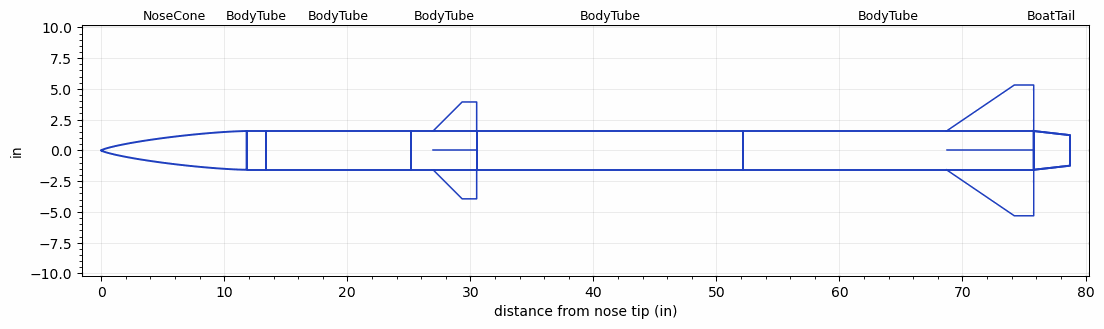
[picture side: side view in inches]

<RASAeroDocument>
 <FileVersion>2</FileVersion>
 <RocketDesign>
  <NoseCone>
   <Length>11.811</Length>
   <Diameter>3.1496</Diameter>
   <Shape>Von Karman Ogive</Shape>
   <Location>0</Location>
  </NoseCone>
  <BodyTube>
   <Length>1.5748</Length>
   <Diameter>3.1496</Diameter>
   <Location>11.811</Location>
  </BodyTube>
  <BodyTube>
   <Length>11.811</Length>
   <Diameter>3.1496</Diameter>
   <Location>13.3858</Location>
  </BodyTube>
  <BodyTube>
   <Length>5.3149</Length>
   <Diameter>3.1496</Diameter>
   <Location>25.1968</Location>
   <Fin>
    <Count>4</Count>
    <Chord>3.5433</Chord>
    <Span>2.3622</Span>
    <SweepDistance>2.3622</SweepDistance>
    <TipChord>1.1811</TipChord>
    <Thickness>0.1181</Thickness>
    <Location>3.5433</Location>
    <AirfoilSection>Subsonic NACA</AirfoilSection>
   </Fin>
  </BodyTube>
  <BodyTube>
   <Length>21.6535</Length>
   <Diameter>3.1496</Diameter>
   <Location>30.5117</Location>
  </BodyTube>
  <BodyTube>
   <Length>23.622</Length>
   <Diameter>3.1496</Diameter>
   <Location>52.1652</Location>
   <BoattailLength>2.9528</BoattailLength>
   <BoattailRearDiameter>2.4803</BoattailRearDiameter>
   <Fin>
    <Count>4</Count>
    <Chord>7.0866</Chord>
    <Span>3.7402</Span>
    <SweepDistance>5.5118</SweepDistance>
    <TipChord>1.5748</TipChord>
    <Thickness>0.1181</Thickness>
    <Location>7.0866</Location>
    <AirfoilSection>Rounded</AirfoilSection>
   </Fin>
  </BodyTube>
  <BoatTail>
   <Length>2.9528</Length>
   <Diameter>3.1496</Diameter>
   <RearDiameter>2.4803</RearDiameter>
   <Location>75.7872</Location>
  </BoatTail>
  <Surface>Rough Camouflage Paint</Surface>
  <ModifiedBarrowman>False</ModifiedBarrowman>
  <Turbulence>False</Turbulence>
  <UseBooster1>False</UseBooster1>
  <UseBooster2>False</UseBooster2>
  <Comments>Ready for PDR!</Comments>
 </RocketDesign>
 <LaunchSite>
  <Altitude>0</Altitude>
  <Pressure>29.9214</Pressure>
  <RodAngle>0</RodAngle>
  <RodLength>157.48</RodLength>
  <Temperature>59</Temperature>
  <WindSpeed>4.4739</WindSpeed>
 </LaunchSite>
 <Recovery>
  <Altitude1>984.252</Altitude1>
  <Altitude2>656.168</Altitude2>
  <DeviceType1>Parachute</DeviceType1>
  <DeviceType2>Parachute</DeviceType2>
  <Event1>True</Event1>
  <Event2>True</Event2>
  <Size1>25.9999</Size1>
  <Size2>15</Size2>
  <EventType1>Altitude</EventType1>
  <EventType2>Apogee</EventType2>
  <CD1>0.75</CD1>
  <CD2>0</CD2>
 </Recovery>
 <SimulationList>
  <Simulation>
   <SustainerLaunchWt>15.1929</SustainerLaunchWt>
   <SustainerCG>47.4662</SustainerCG>
   <SustainerIgnitionDelay>0</SustainerIgnitionDelay>
   <Booster1SeparationDelay>0</Booster1SeparationDelay>
   <Booster1IgnitionDelay>0</Booster1IgnitionDelay>
   <IncludeBooster1>False</IncludeBooster1>
   <Booster2Delay>0</Booster2Delay>
   <IncludeBooster2>False</IncludeBooster2>
  </Simulation>
  <Simulation>
   <SustainerLaunchWt>15.1929</SustainerLaunchWt>
   <SustainerCG>47.4662</SustainerCG>
   <SustainerIgnitionDelay>0</SustainerIgnitionDelay>
   <Booster1SeparationDelay>0</Booster1SeparationDelay>
   <Booster1IgnitionDelay>0</Booster1IgnitionDelay>
   <IncludeBooster1>False</IncludeBooster1>
   <Booster2Delay>0</Booster2Delay>
   <IncludeBooster2>False</IncludeBooster2>
  </Simulation>
  <Simulation>
   <SustainerLaunchWt>15.1929</SustainerLaunchWt>
   <SustainerCG>47.4662</SustainerCG>
   <SustainerIgnitionDelay>0</SustainerIgnitionDelay>
   <Booster1SeparationDelay>0</Booster1SeparationDelay>
   <Booster1IgnitionDelay>0</Booster1IgnitionDelay>
   <IncludeBooster1>False</IncludeBooster1>
   <Booster2Delay>0</Booster2Delay>
   <IncludeBooster2>False</IncludeBooster2>
  </Simulation>
 </SimulationList>
</RASAeroDocument>
